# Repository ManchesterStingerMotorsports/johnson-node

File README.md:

# Pressure sensor meeting example

Pressure sensor → ADC A / IN1 → ADCSample → queue → CAN

Start in [main/main.cpp](main/main.cpp): it creates the queue and starts two tasks.

- [ADC task](main/tasks/ADC/ADC_task.cpp): reads the pressure sensor every 100 ms
  and queues its raw count in ADCSample's raw[0].
- [CAN task](main/tasks/CAN/CAN_task.cpp): takes each sample, packs it and sends it.

- [main/data/ADCSample.hpp](main/data/ADCSample.hpp): existing sample structure.
- [main/config/BoardConfig.hpp](main/config/BoardConfig.hpp): ADC and CAN wiring.
- libraries/: the ADC124S051 and MSM_CAN drivers used by the example.

## Build

Use an ESP-IDF 5.5.2 terminal in this folder:

~~~sh
idf.py set-target esp32s3
idf.py build
~~~

## CAN frame

ID 0x500, eight bytes. Bytes 0–1 contain raw[0] as an unsigned 16-bit,
big-endian value; bytes 2–7 are zero. A raw count of 2068 gives:

~~~text
08 14 00 00 00 00 00 00
~~~

This sends raw ADC counts. The board ADC reference is 5 V; convert to pressure
using the actual sensor calibration and input circuit.

## Scheduled-send alternative

The running example uses send_msg(frame). To use the other method from the
slides, declare bool scheduled = false before the CAN task's loop and replace
the send_msg call with:

~~~cpp
esp_err_t result;
if (!scheduled)
{
    result = MSM_CAN::schedule(frame, 100);
    scheduled = (result == ESP_OK);
}
else
{
    result = MSM_CAN::update_scheduled_payload(frame);
}
~~~

This schedules once, then updates the payload as samples arrive.
If readings stop, the last payload continues to transmit.

## Optional receive setup

For a receive example, put MSM_CAN::set_hardware_filters(0x200) before init(),
then ESP_ERROR_CHECK(MSM_CAN::subscribe(0x200)) after init().

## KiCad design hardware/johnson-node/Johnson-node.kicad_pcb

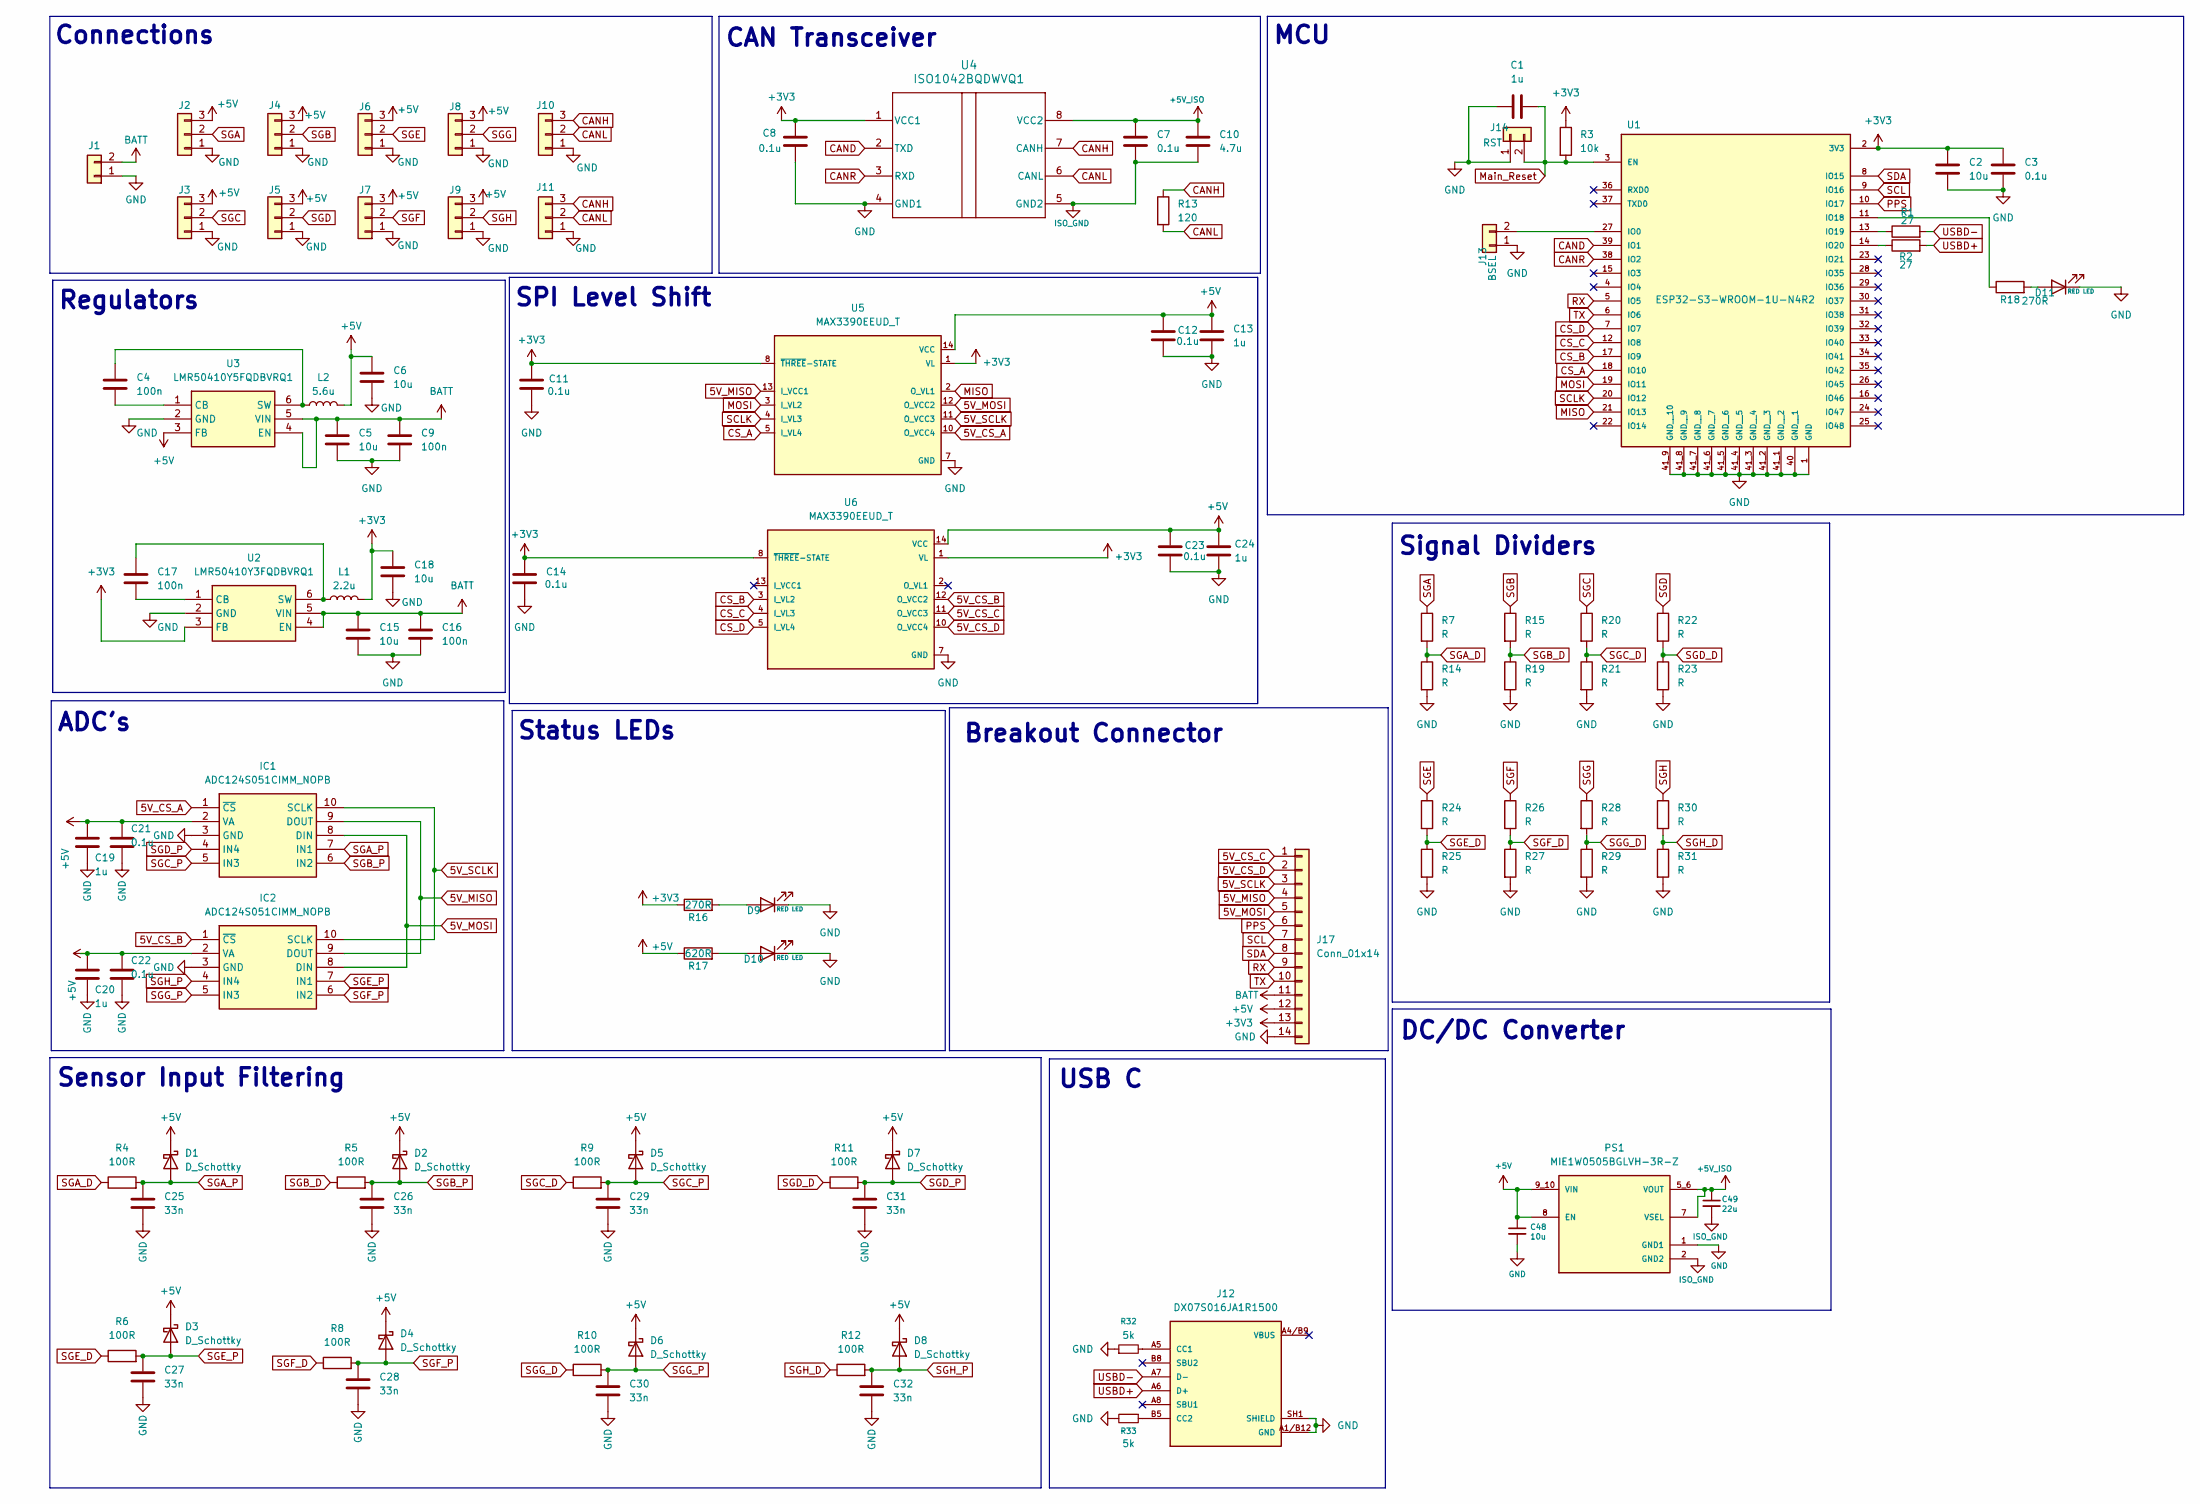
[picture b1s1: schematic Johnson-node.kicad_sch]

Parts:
C1, C13, C19, C20, C24: 1u; C_0603_1608Metric
C2, C5, C6, C15, C18, C48: 10u; C_0603_1608Metric
C3, C7, C8, C11, C12, C14, C21, C22, C23: 0.1u; C_0603_1608Metric
C4, C9, C16, C17: 100n; C_0603_1608Metric
C10: 4.7u; C_0603_1608Metric
C25, C26, C27, C28, C29, C30, C31, C32: 33n; C_0603_1608Metric
C49: 22u; C_0603_1608Metric
D1, D2, D3, D4, D5, D6, D7, D8: D_Schottky; D_0603_1608Metric
D9, D10, D11: RED LED; LED_0603_1608Metric; Part Number AP2012EC
IC1, IC2: ADC124S051CIMM_NOPB; SOP50P490X110-10N; Mouser Part Number 926-AD124S051CIMMNPB
J1: Conn_01x02; JST_XA_S02B-XASK-1_1x02_P2.50mm_Horizontal
J2, J3, J4, J5, J6, J7, J8, J9, J10, J11: Conn_01x03; JST_XA_S03B-XASK-1_1x03_P2.50mm_Horizontal
J12: DX07S016JA1R1500; JAE_DX07S016JA1R1500; PARTREV 3
J13: BSEL; PinHeader_1x02_P2.54mm_Vertical
J14: RST; PinHeader_1x02_P2.54mm_Vertical
J17: Conn_01x14; JST_XA_B14B-XASK-1_1x14_P2.50mm_Vertical
L1: 2.2u; WE-TPC_4828
L2: 5.6u; WE-TPC_4828
PS1: MIE1W0505BGLVH-3R-Z; CONV_MIE1W0505BGLVH-3R-Z; PARTREV 0.8; DigiKey_Part_Number 1589-MIE1W0505BGLVH-3R-ZCT-ND
R1, R2: 27; R_0603_1608Metric
R3: 10k; R_0603_1608Metric
R4, R5, R6, R8, R9, R10, R11, R12: 100R; R_0603_1608Metric
R7, R14, R15, R19, R20, R21, R22, R23, R24, R25, R26, R27, R28, R29, R30, R31: R; R_0805_2012Metric
R13: 120; R_0603_1608Metric
R16, R18: 270R; R_0603_1608Metric; Part Number RC0805FR-07270RL
R17: 620R; R_0603_1608Metric; Part Number RC0805FR-07270RL
R32, R33: 5k; R_0603_1608Metric
U1: ESP32-S3-WROOM-1U-N4R2; XCVR_ESP32-S3-WROOM-1U-N16R8; PARTREV v1.1
U2: LMR50410Y3FQDBVRQ1; DBV0006A-MFG; Mouser Part Number 595-R50410Y3FQDBVRQ1
U3: LMR50410Y5FQDBVRQ1; DBV0006A-MFG; Mouser Part Number 595-R50410Y3FQDBVRQ1
U4: ISO1042BQDWVQ1; DWV0008A-MFG
U5, U6: MAX3390EEUD_T; SOP65P640X110-14N

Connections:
5V_CS_A: IC1.1 (~CS), U5.10 (O_VCC4)
5V_CS_B: IC2.1 (~CS), U6.12 (O_VCC2)
5V_CS_C: J17.1, U6.11 (O_VCC3)
5V_CS_D: J17.2, U6.10 (O_VCC4)
5V_MISO: IC1.9 (DOUT), IC2.9 (DOUT), J17.4, U5.13 (I_VCC1)
5V_MOSI: IC1.8 (DIN), IC2.8 (DIN), J17.5, U5.12 (O_VCC2)
5V_SCLK: IC1.10 (SCLK), IC2.10 (SCLK), J17.3, U5.11 (O_VCC3)
+3V3: C2.2, C3.2, C8.2, C11.1, C14.1, C18.1, J17.13, L1.2, R3.1, R16.1, U1.2 (3V3), U2.3 (FB), U4.1 (VCC1), U5.1 (VL), U5.8 (~THREE-STATE), U6.1 (VL), U6.8 (~THREE-STATE)
+5V: C6.1, C12.1, C13.1, C19.1, C20.1, C21.1, C22.1, C23.1, C24.1, C48.1, D1.1 (K), D2.1 (K), D3.1 (K), D4.1 (K), D5.1 (K), D6.1 (K), D7.1 (K), D8.1 (K), IC1.2 (VA), IC2.2 (VA), J2.3, J3.3, J4.3, J5.3, J6.3, J7.3, J8.3, J9.3, J17.12, L2.2, PS1.8 (EN), PS1.9_10 (VIN), R17.1, U3.3 (FB), U5.14 (VCC), U6.14 (VCC)
+5V_ISO: C7.2, C10.2, C49.1, PS1.5_6 (VOUT), PS1.7 (VSEL), U4.8 (VCC2)
BATT: C5.1, C9.1, C15.1, C16.1, J1.2, J17.11, U2.4 (EN), U2.5 (VIN), U3.4 (EN), U3.5 (VIN)
CAND: U1.39 (IO1), U4.2 (TXD)
CANH: J10.3, J11.3, R13.1, U4.7 (CANH)
CANL: J10.2, J11.2, R13.2, U4.6 (CANL)
CANR: U1.38 (IO2), U4.3 (RXD)
CS_A: U1.18 (IO10), U5.5 (I_VL4)
CS_B: U1.17 (IO9), U6.3 (I_VL2)
CS_C: U1.12 (IO8), U6.4 (I_VL3)
CS_D: U1.7 (IO7), U6.5 (I_VL4)
GND: C1.1, C2.1, C3.1, C5.2, C6.2, C8.1, C9.2, C11.2, C12.2, C13.2, C14.2, C15.2, C16.2, C18.2, C19.2, C20.2, C21.2, C22.2, C23.2, C24.2, C25.2, C26.2, C27.2, C28.2, C29.2, C30.2, C31.2, C32.2, C48.2, D9.1 (K), D10.1 (K), D11.1 (K), IC1.3 (GND), IC2.3 (GND), J1.1, J2.1, J3.1, J4.1, J5.1, J6.1, J7.1, J8.1, J9.1, J10.1, J11.1, J12.A1/B12 (GND), J12.A12/B1 (GND), J12.SH1 (SHIELD), J12.SH2 (SHIELD), J12.SH3 (SHIELD), J12.SH4 (SHIELD), J12.SH5 (SHIELD), J12.SH6 (SHIELD), J13.1, J14.1, J17.14, PS1.1 (GND1), PS1.11_12 (GND1), R14.2, R19.2, R21.2, R23.2, R25.2, R27.2, R29.2, R31.2, R32.1, R33.2, U1.1 (GND), U1.40 (GND__1), U1.41_1 (GND__2), U1.41_2 (GND__3), U1.41_3 (GND__4), U1.41_4 (GND__5), U1.41_5 (GND__6), U1.41_6 (GND__7), U1.41_7 (GND__8), U1.41_8 (GND__9), U1.41_9 (GND__10), U1.41_10, U1.41_11, U1.41_12, U1.41_13, U1.41_14, U1.41_15, U1.41_16, U1.41_17, U1.41_18, U1.41_19, U1.41_20, U1.41_21, U2.2 (GND), U3.2 (GND), U4.4 (GND1), U5.7 (GND), U6.7 (GND)
ISO_GND: C7.1, C10.1, C49.2, PS1.2 (GND2), PS1.3_4 (GND2), U4.5 (GND2)
MISO: U1.21 (IO13), U5.2 (O_VL1)
MOSI: U1.19 (IO11), U5.3 (I_VL2)
Main_Reset: C1.2, J14.2, R3.2, U1.3 (EN)
unnamed: D9.2 (A), R16.2
unnamed: D10.2 (A), R17.2
unnamed: D11.2 (A), R18.2
unnamed: J12.A5 (CC1), R32.2
unnamed: J12.B5 (CC2), R33.1
unnamed: J13.2, U1.27 (IO0)
unnamed: R18.1, U1.11 (IO18)
unnamed: R1.1, U1.13 (IO19)
unnamed: R2.1, U1.14 (IO20)
unnamed: C17.2, U2.1 (CB)
unnamed: C17.1, L1.1, U2.6 (SW)
unnamed: C4.2, U3.1 (CB)
unnamed: C4.1, L2.1, U3.6 (SW)
PPS: J17.6, U1.10 (IO17)
RX: J17.9, U1.5 (IO5)
SCL: J17.7, U1.9 (IO16)
SCLK: U1.20 (IO12), U5.4 (I_VL3)
SDA: J17.8, U1.8 (IO15)
SGA: J2.2, R7.1
SGA_D: R4.1, R7.2, R14.1
SGA_P: C25.1, D1.2 (A), IC1.7 (IN1), R4.2
SGB: J4.2, R15.1
SGB_D: R5.1, R15.2, R19.1
SGB_P: C26.1, D2.2 (A), IC1.6 (IN2), R5.2
SGC: J3.2, R20.1
SGC_D: R9.1, R20.2, R21.1
SGC_P: C29.1, D5.2 (A), IC1.5 (IN3), R9.2
SGD: J5.2, R22.1
SGD_D: R11.1, R22.2, R23.1
SGD_P: C31.1, D7.2 (A), IC1.4 (IN4), R11.2
SGE: J6.2, R24.1
SGE_D: R6.1, R24.2, R25.1
SGE_P: C27.1, D3.2 (A), IC2.7 (IN1), R6.2
SGF: J7.2, R26.1
SGF_D: R8.1, R26.2, R27.1
SGF_P: C28.1, D4.2 (A), IC2.6 (IN2), R8.2
SGG: J8.2, R28.1
SGG_D: R10.1, R28.2, R29.1
SGG_P: C30.1, D6.2 (A), IC2.5 (IN3), R10.2
SGH: J9.2, R30.1
SGH_D: R12.1, R30.2, R31.1
SGH_P: C32.1, D8.2 (A), IC2.4 (IN4), R12.2
TX: J17.10, U1.6 (IO6)
USBD+: J12.A6 (D+), J12.B6 (D+), R2.2
USBD-: J12.A7 (D-), J12.B7 (D-), R1.2

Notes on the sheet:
MCU
SPI Level Shift
Sensor Input Filtering
Status LEDs
Regulators
Connections
ADC's
CAN Transceiver
Breakout Connector
DC/DC Converter
Signal Dividers
USB C

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
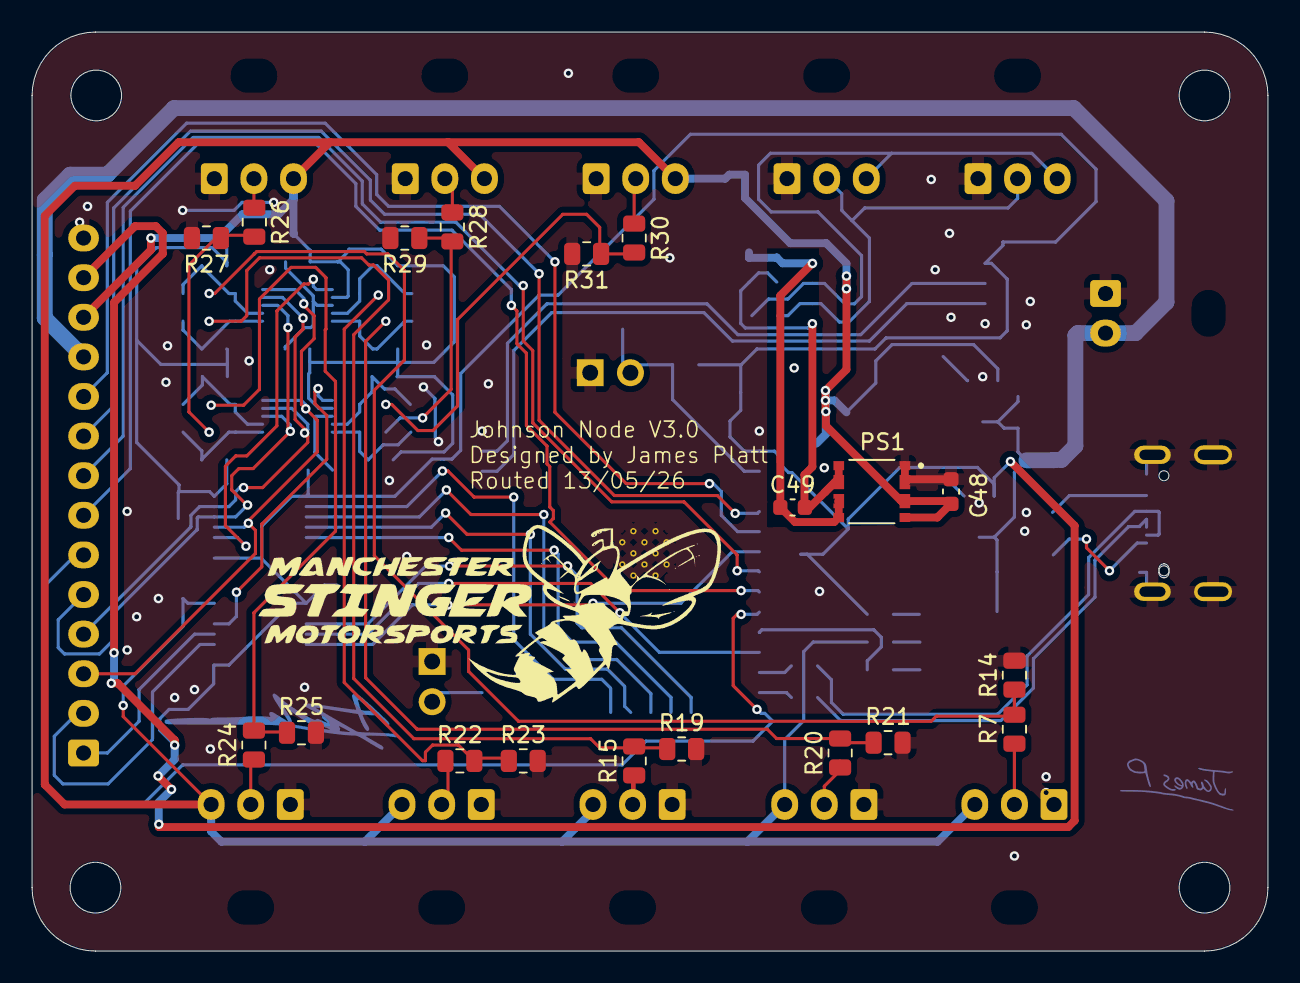
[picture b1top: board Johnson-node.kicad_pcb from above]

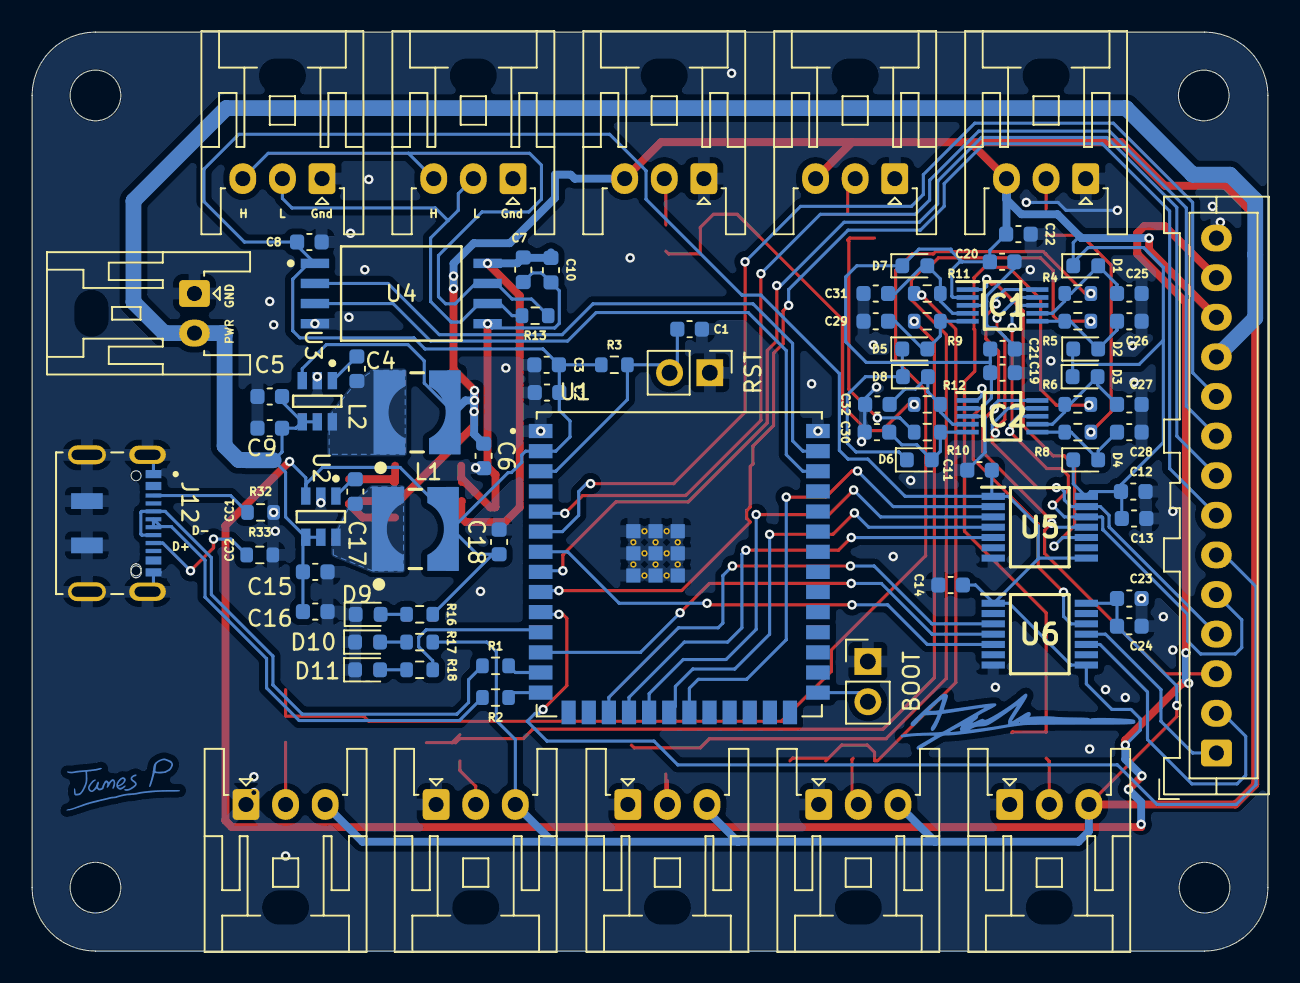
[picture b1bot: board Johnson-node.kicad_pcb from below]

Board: 4 copper layers, 78.0 x 58.0 mm, 104 parts (85 on the bottom side), 69 nets.

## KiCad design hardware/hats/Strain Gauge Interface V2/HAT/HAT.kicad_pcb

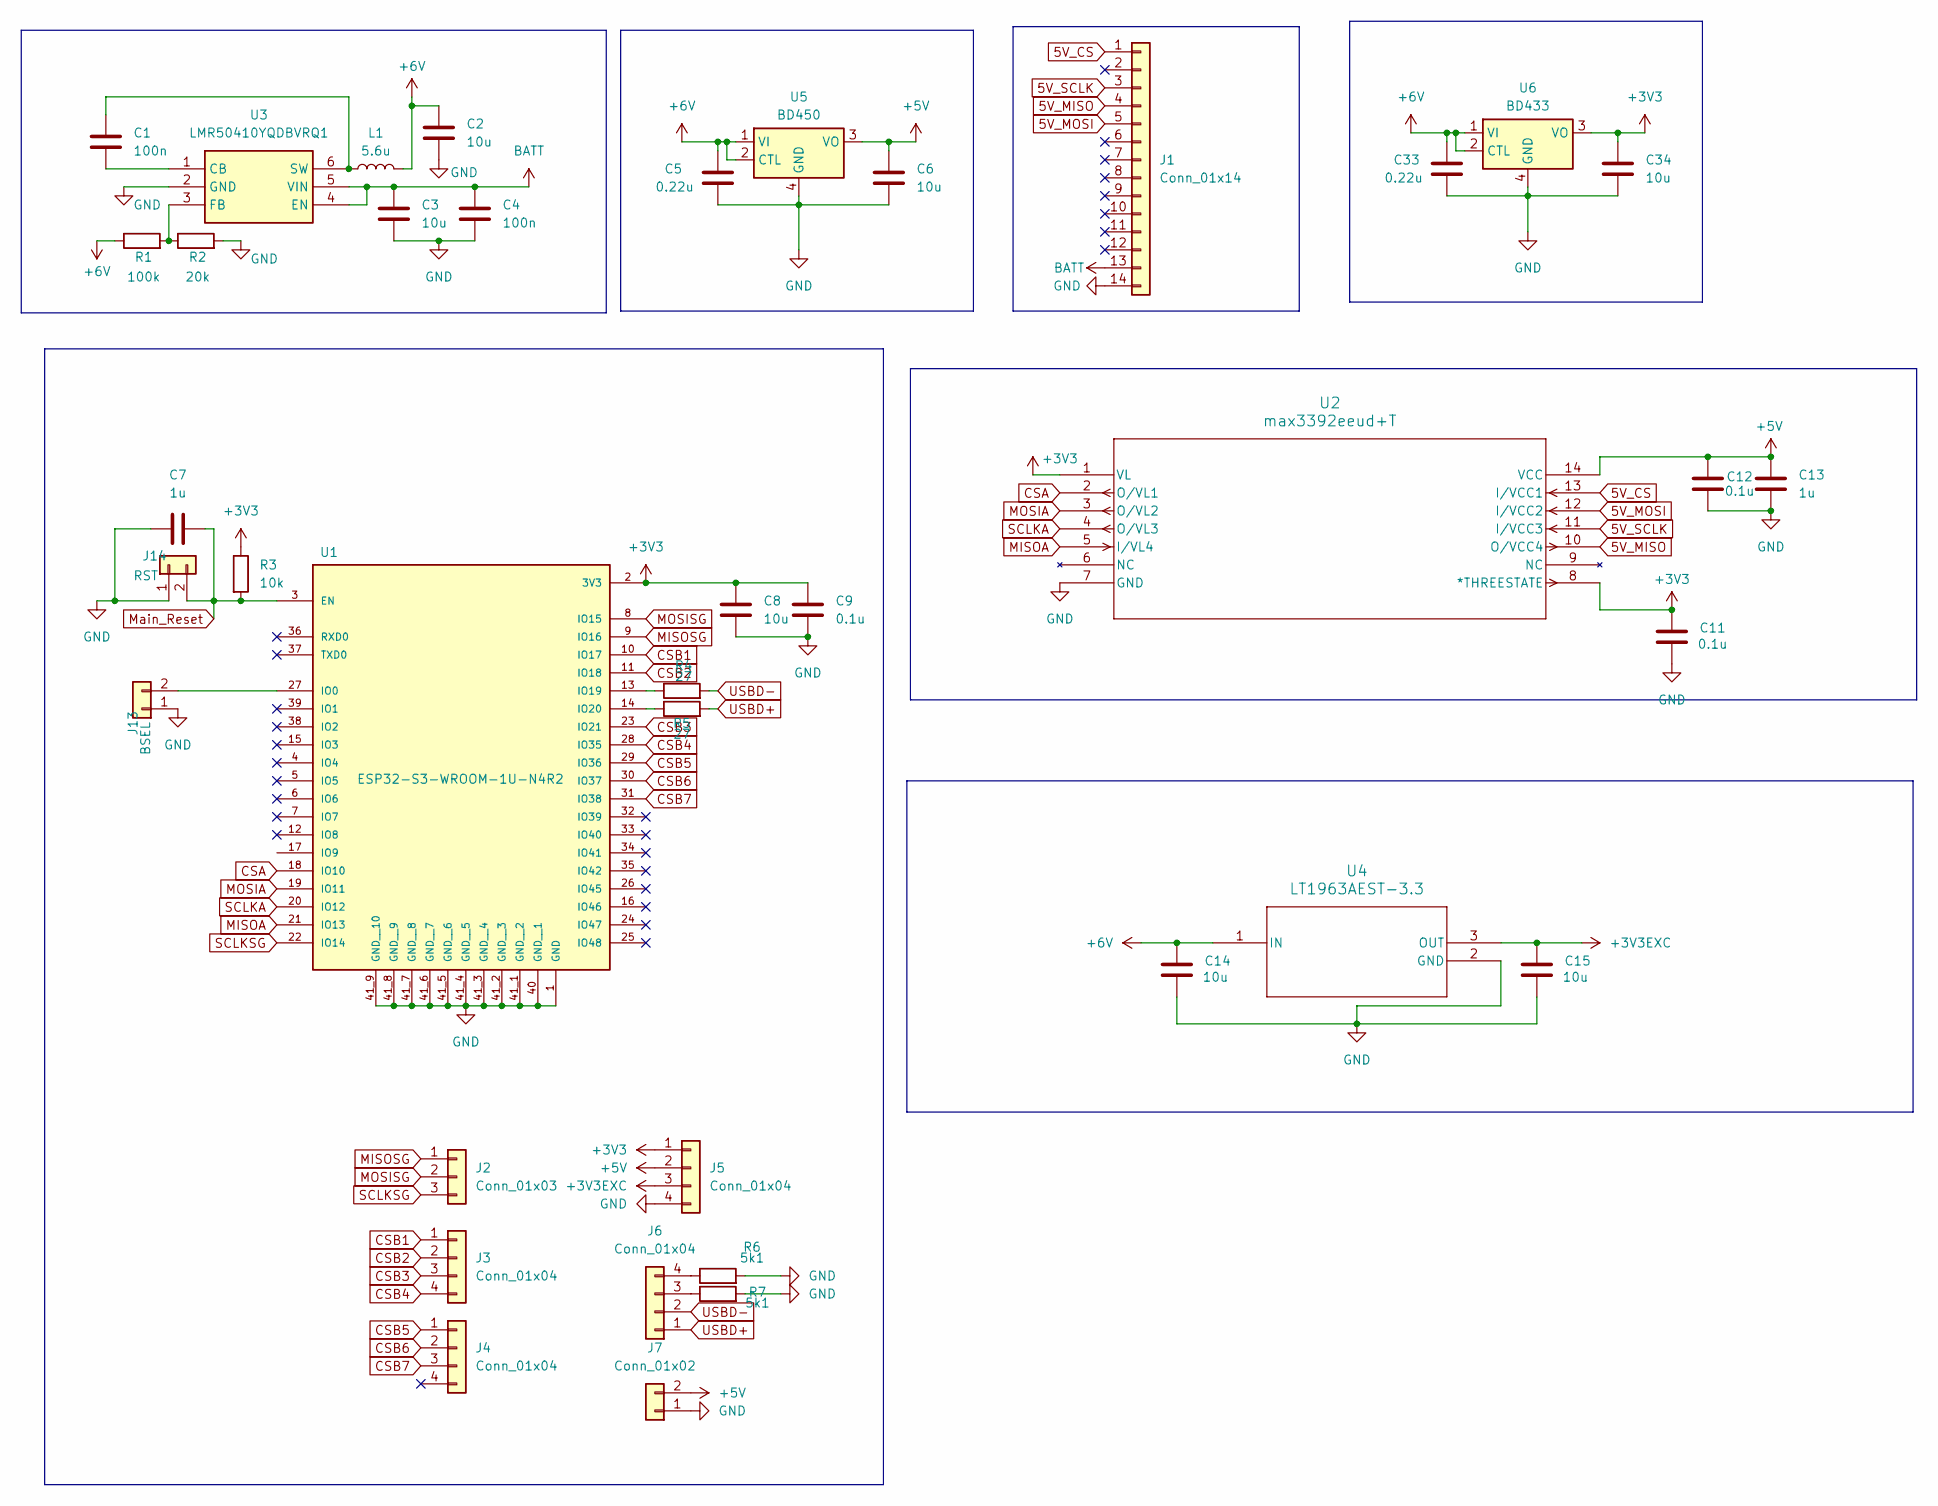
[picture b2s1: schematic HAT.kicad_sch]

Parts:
C1, C4: 100n; C_0603_1608Metric
C2, C3, C6, C8, C14, C15, C34: 10u; C_0603_1608Metric
C5, C33: 0.22u; C_0603_1608Metric
C7, C13: 1u; C_0603_1608Metric
C9, C11, C12: 0.1u; C_0603_1608Metric
J1: Conn_01x14; JST_XA_S14B-XASK-1_1x14_P2.50mm_Horizontal
J2: Conn_01x03; JST_XA_S03B-XASK-1_1x03_P2.50mm_Horizontal
J3, J4, J5, J6: Conn_01x04; JST_XA_S04B-XASK-1_1x04_P2.50mm_Horizontal
J7: Conn_01x02; JST_XA_S02B-XASK-1_1x02_P2.50mm_Horizontal
J13: BSEL; PinHeader_1x02_P2.54mm_Vertical
J14: RST; PinHeader_1x02_P2.54mm_Vertical
L1: 5.6u; WE-TPC_4828
R1: 100k; R_0603_1608Metric
R2: 20k; R_0603_1608Metric
R3: 10k; R_0603_1608Metric
R4, R5: 27; R_0603_1608Metric
R6, R7: 5k1; R_0603_1608Metric
U1: ESP32-S3-WROOM-1U-N4R2; XCVR_ESP32-S3-WROOM-1U-N16R8; PARTREV v1.1
U2: max3392eeud+T; 21-0066J_14_MXM
U3: LMR50410YQDBVRQ1; Regulator_Switching_SOT-23-6; Mouser Part Number 595-R50410Y3FQDBVRQ1
U4: LT1963AEST-3.3; SOT-223-3_TabPin2
U5: BD450; Regulator_Linear_SOT-223-4
U6: BD433; Regulator_Linear_SOT-223-4

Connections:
5V_CS: J1.1, U2.13 (I/VCC1)
5V_MISO: J1.4, U2.10 (O/VCC4)
5V_MOSI: J1.5, U2.12 (I/VCC2)
5V_SCLK: J1.3, U2.11 (I/VCC3)
+3V3: C8.2, C9.2, C11.1, C34.1, J5.1, R3.1, U1.2 (3V3), U2.1 (VL), U2.8 (*THREESTATE), U6.3 (VO)
+3V3EXC: C15.1, J5.3, U4.3 (OUT)
+5V: C6.1, C12.1, C13.1, J5.2, J7.2, U2.14 (VCC), U5.3 (VO)
+6V: C2.1, C5.1, C14.1, C33.1, L1.2, R1.1, U4.1 (IN), U5.1 (VI), U5.2 (CTL), U6.1 (VI), U6.2 (CTL)
BATT: C3.1, C4.1, J1.13, U3.4 (EN), U3.5 (VIN)
CSA: U1.18 (IO10), U2.2 (O/VL1)
CSB1: J3.1, U1.10 (IO17)
CSB2: J3.2, U1.11 (IO18)
CSB3: J3.3, U1.23 (IO21)
CSB4: J3.4, U1.28 (IO35)
CSB5: J4.1, U1.29 (IO36)
CSB6: J4.2, U1.30 (IO37)
CSB7: J4.3, U1.31 (IO38)
GND: C2.2, C3.2, C4.2, C5.2, C6.2, C7.1, C8.1, C9.1, C11.2, C12.2, C13.2, C14.2, C15.2, C33.2, C34.2, J1.14, J5.4, J7.1, J13.1, J14.1, R2.2, R6.2, R7.2, U1.1 (GND), U1.40 (GND__1), U1.41_1 (GND__2), U1.41_2 (GND__3), U1.41_3 (GND__4), U1.41_4 (GND__5), U1.41_5 (GND__6), U1.41_6 (GND__7), U1.41_7 (GND__8), U1.41_8 (GND__9), U1.41_9 (GND__10), U2.7 (GND), U3.2 (GND), U4.2 (GND), U5.4 (GND), U6.4 (GND)
MISOA: U1.21 (IO13), U2.5 (I/VL4)
MISOSG: J2.1, U1.9 (IO16)
MOSIA: U1.19 (IO11), U2.3 (O/VL2)
MOSISG: J2.2, U1.8 (IO15)
Main_Reset: C7.2, J14.2, R3.2, U1.3 (EN)
unnamed: J6.3, R7.1
unnamed: J6.4, R6.1
unnamed: J13.2, U1.27 (IO0)
unnamed: R4.1, U1.13 (IO19)
unnamed: R5.1, U1.14 (IO20)
unnamed: C1.2, U3.1 (CB)
unnamed: R1.2, R2.1, U3.3 (FB)
unnamed: C1.1, L1.1, U3.6 (SW)
SCLKA: U1.20 (IO12), U2.4 (O/VL3)
SCLKSG: J2.3, U1.22 (IO14)
USBD+: J6.1, R5.2
USBD-: J6.2, R4.2

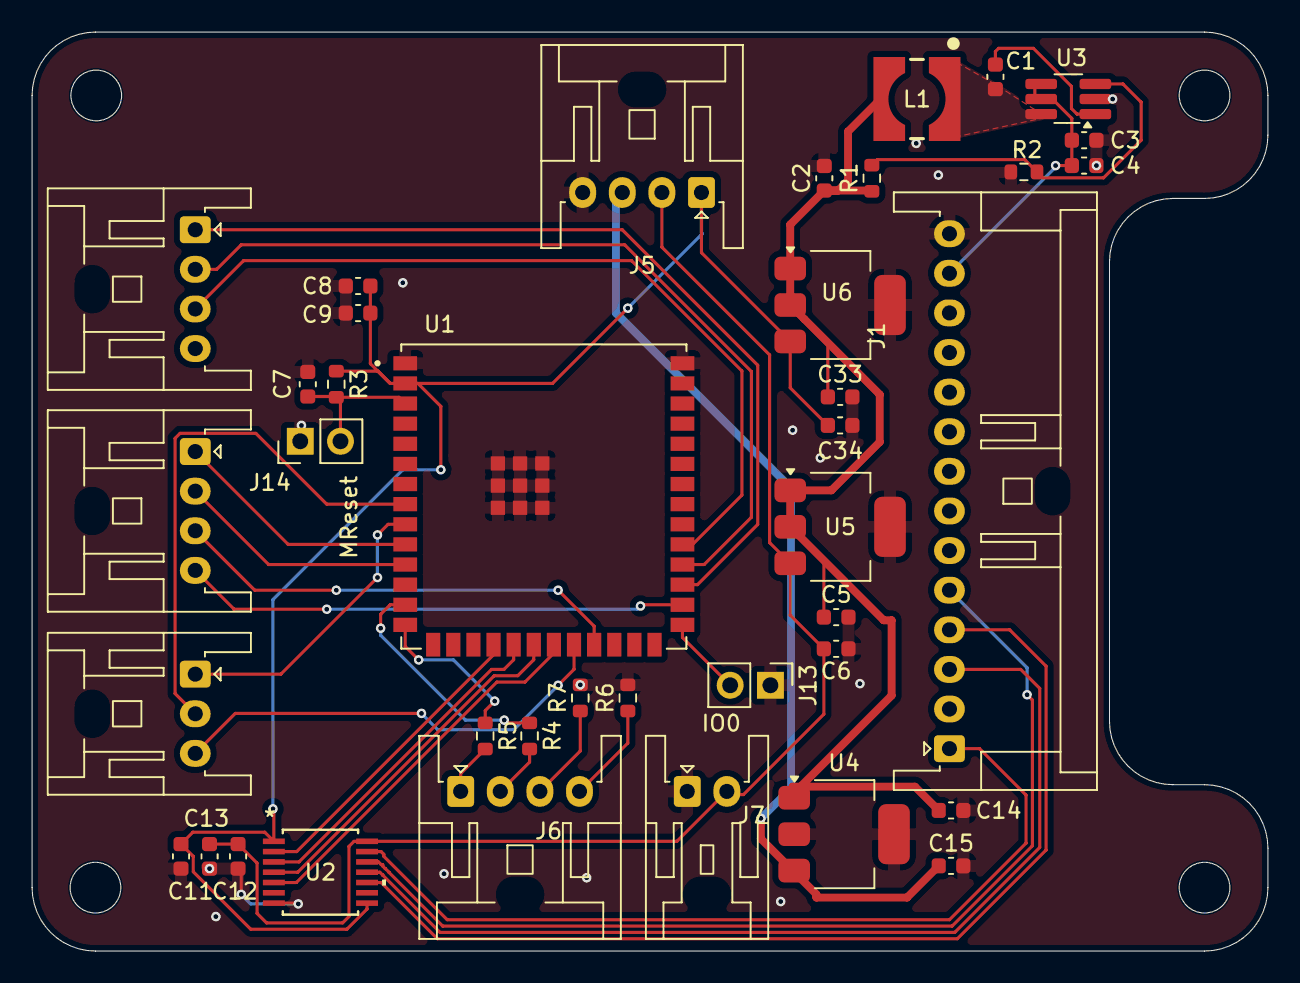
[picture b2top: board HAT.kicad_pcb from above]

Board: 2 copper layers, 78.0 x 58.0 mm, 39 parts (0 on the bottom side), 35 nets.

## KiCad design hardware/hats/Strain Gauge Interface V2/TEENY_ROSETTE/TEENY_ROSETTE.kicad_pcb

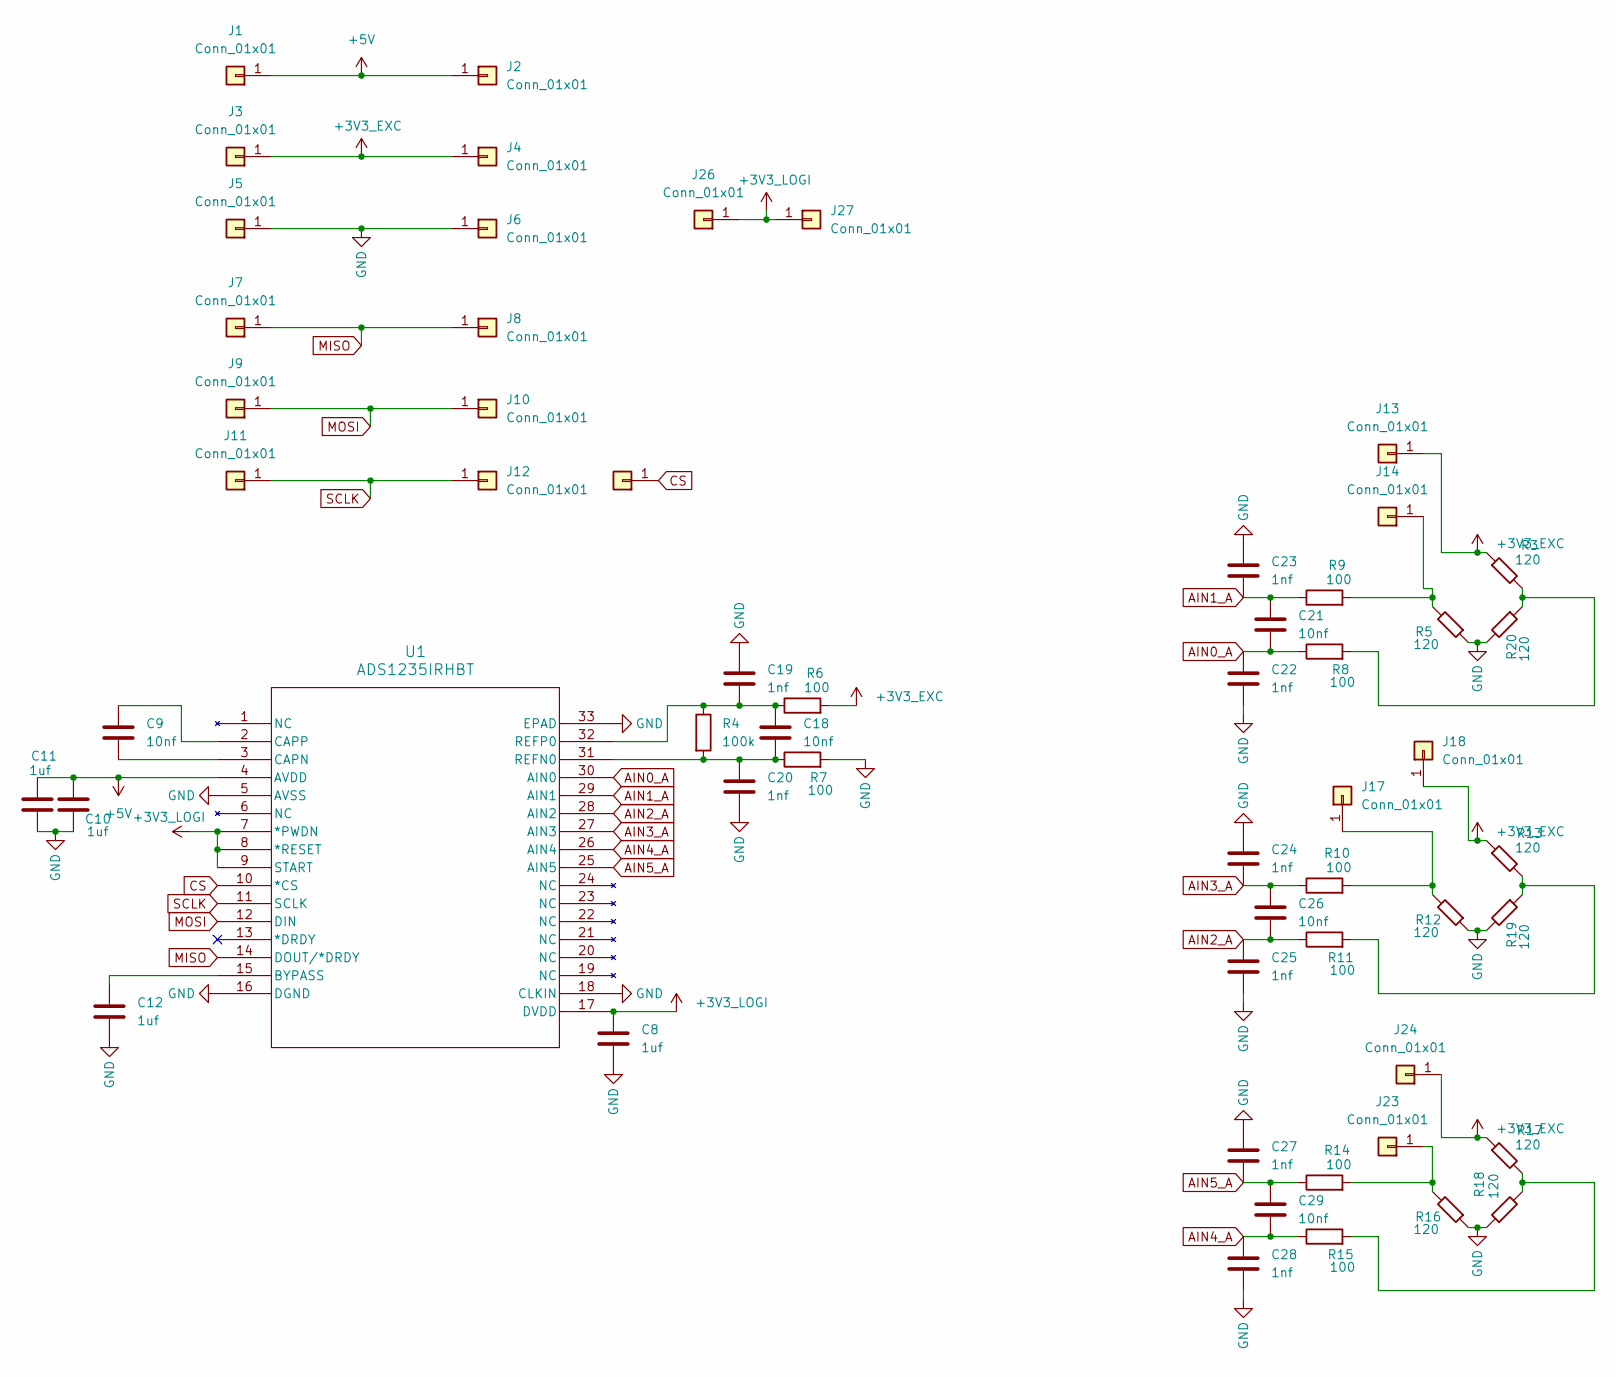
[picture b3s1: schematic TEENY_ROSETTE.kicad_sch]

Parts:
C8, C10, C11, C12: 1uf; C_0603_1608Metric
C9, C18, C21, C26, C29: 10nf; C_0603_1608Metric
C19, C20, C22, C23, C24, C25, C27, C28: 1nf; C_0603_1608Metric
J1, J2, J3, J4, J5, J6, J7, J8, J9, J10, J11, J12, J13, J14, J17, J18, J23, J24, J25, J26, J27: Conn_01x01; PAD
R3, R5, R12, R13, R16, R17, R18, R19, R20: 120; R_0603_1608Metric
R4: 100k; R_0603_1608Metric
R6, R7, R8, R9, R10, R11, R14, R15: 100; R_0603_1608Metric
U1: ADS1235IRHBT; RHB32_TEX

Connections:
+3V3_EXC: J3.1 (Pin_1_1), J4.1 (Pin_1_1), J13.1 (Pin_1_1), J18.1 (Pin_1_1), J24.1 (Pin_1_1), R3.1, R6.2, R13.1, R17.1
+3V3_LOGI: C8.1, J26.1 (Pin_1_1), J27.1 (Pin_1_1), U1.7 (*PWDN), U1.8 (*RESET), U1.9 (START), U1.17 (DVDD)
+5V: C10.1, C11.1, J1.1 (Pin_1_1), J2.1 (Pin_1_1), U1.4 (AVDD)
AIN0_A: C21.2, C22.1, R8.1, U1.30 (AIN0)
AIN1_A: C21.1, C23.2, R9.1, U1.29 (AIN1)
AIN2_A: C25.1, C26.2, R11.1, U1.28 (AIN2)
AIN3_A: C24.2, C26.1, R10.1, U1.27 (AIN3)
AIN4_A: C28.1, C29.2, R15.1, U1.26 (AIN4)
AIN5_A: C27.2, C29.1, R14.1, U1.25 (AIN5)
CS: J25.1 (Pin_1_1), U1.10 (*CS)
GND: C8.2, C10.2, C11.2, C12.2, C19.1, C20.2, C22.2, C23.1, C24.1, C25.2, C27.1, C28.2, J5.1 (Pin_1_1), J6.1 (Pin_1_1), R5.1, R7.2, R12.1, R16.1, R18.1, R19.2, R20.2, U1.5 (AVSS), U1.16 (DGND), U1.18 (CLKIN), U1.33 (EPAD)
MISO: J7.1 (Pin_1_1), J8.1 (Pin_1_1), U1.14 (DOUT/*DRDY)
MOSI: J9.1 (Pin_1_1), J10.1 (Pin_1_1), U1.12 (DIN)
unnamed: J14.1 (Pin_1_1), R5.2, R9.2
unnamed: J17.1 (Pin_1_1), R10.2, R12.2
unnamed: J23.1 (Pin_1_1), R14.2, R16.2
unnamed: R11.2, R13.2, R19.1
unnamed: R15.2, R17.2, R18.2
unnamed: R3.2, R8.2, R20.1
unnamed: C12.1, U1.15 (BYPASS)
unnamed: C9.2, U1.3 (CAPN)
unnamed: C9.1, U1.2 (CAPP)
unnamed: C18.2, C20.1, R4.2, R7.1, U1.31 (REFN0)
unnamed: C18.1, C19.2, R4.1, R6.1, U1.32 (REFP0)
SCLK: J11.1 (Pin_1_1), J12.1 (Pin_1_1), U1.11 (SCLK)

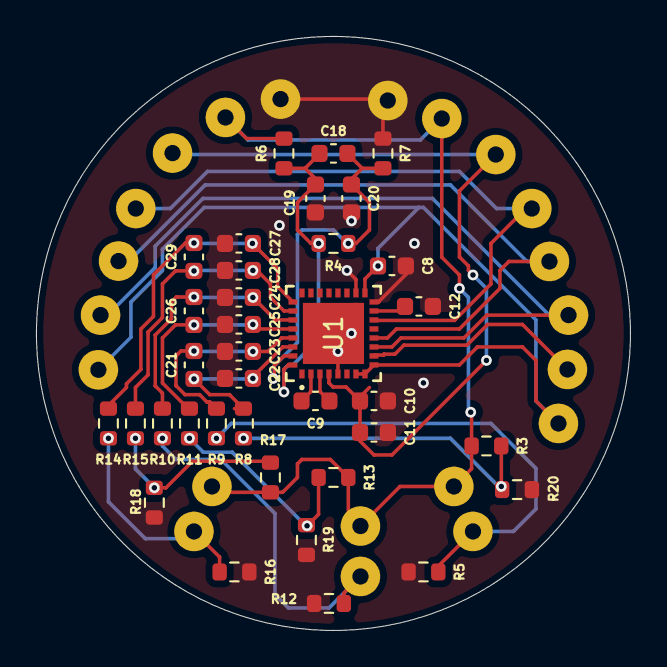
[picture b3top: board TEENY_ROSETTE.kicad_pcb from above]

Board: 2 copper layers, 33.0 x 33.0 mm, 57 parts (0 on the bottom side), 25 nets.
